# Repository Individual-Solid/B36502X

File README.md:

# BE6502X-SBC

## Overview
The BE6502X-SBC is an extensible single board computer, based on the "Hello World"
video tutorial by Ben Eater, and the "Potporri" computer design by Garth Wilson.

The computer features a W65c02 8-bit microprocessor running at 1Mhz, 32kb static 
RAM, 32kb EEPROM, two 8-bit GPIO ports, an onboard power supervisor, and a 40-pin
expansion bus.

The computer is "software compatible" with the programs Ben Eater builds in his
Youtube series. 

### Major Differences from the Ben Eater 6502 reference schematic
- Pull-up resistors on all active-low input signals (/NMI, /BE, etc...)
- Proper debounced reset pushbutton and power-on-reset circuit.
- Barrel jack 5v power connector, power LED, reset LED, SYNC LED, and switch.
- All 16 GPIO and 4 Control signals from the VIA are exposed through two
  14-pin shrouded pin IDC headers, CA2 also has an onboard LED.
- LCD, push-buttons, and 8-bit LED output are moved to an expansion board.
- Selector for 65c22 VIAs IRQ pin connection to processor /IRQ or /NMI

### Major Differences from the Garth Wilson 6502 reference schematic
- Clock option chosen is the Can Oscillator. Reset circuit chosen is DS1813.
- Because of these choices, an 74HC00 can be used for address decoding instead 
  of the '132
- Permanently configured for the WDC65c02 processor, 28C256 EEPROM.

## IO Ports
There are two onboard 8-bit IO ports connected to a W65c22S. Each port has an additional
two control lines. Each port has a 14-pin IDC male socket with the following pinout.
|Func|Pin#|Pin#|Func|
|----|-|-|---|
|GND|1|2|5V|
|Px0|3|4|Px1|
|Px2|5|6|Px3|
|Px4|7|8|Px5|
|Px6|9|10|Px7|
|Cx1|11|12|Cx2|
|5V|13|14|GND|

CA2 has an onboard indicator LED, but the pin can easily be repurposed.

## Bus

The BE6502X family sports a 40-pin extension bus. This bus is hardware compatible 
with RC2014 backplanes, although pin assignment is different. There's an existing 
small ecosystem of boards using the "RC6502" bus layout, but I invented my own 
think that felt natural to me. The original RC2014 bus has a lot of Z80/8080 
exclusive signals.

|Pin|BE6502X|RC6502|RC2014|Notes (primarily differences from RC6502)|
|-----|-------|------|------|-----|
| 1|A15|A15|A15||
| 2|A14|A14|A14||
| 3|A13|A13|A13||
| 4|A12|A12|A12||
| 5|A11|A11|A11||
| 6|A10|A10|A10||
| 7|A9|A9|A9||
| 8|A8|A8|A8||
| 9|A7|A7|A7||
|10|A6|A6|A6||
|11|A5|A5|A5||
|12|A4|A4|A4||
|13|A3|A3|A3||
|14|A2|A2|A2||
|15|A1|A1|A1||
|16|A0|A0|A0||
|17|GND|GND|GND||
|18|VCC|VCC|VCC||
|19|/MLB|PHI2O|/M1|See CLK for why it's not PHI2O. 6502 has no /M1. This could be SYNC, but /MLB is more interesting for DMA|
|20|/RESET|/RESET|/RESET||
|21|CLK|PHI0I|CLK|Using PHI1 in and PHI2 out is not supported for the new W65c22 chips used in the Eater kit. Just using PHI2 as CLK opens up an additional signal.|
|22|/IRQ|/IRQ|/INT||
|23|/BE|PHI1I (but really,EX0)|/MREQ|Dedicated /BE line for DMA|
|24|RWB|RWB|/WR||
|25|RDY|RDY|/RD||
|26|EX0|SYNC|/IOREQ|SYNC on the bus isn't particularly useful, compared to having an easy EX pin which you can easily connect to /IOEN|
|27|D0|D0|D0||
|28|D1|D1|D1||
|29|D2|D2|D2||
|30|D3|D3|D3||
|31|D4|D4|D4||
|32|D5|D5|D5||
|33|D6|D6|D6||
|34|D7|D7|D7||
|35|SDA|Tx|Tx|Putting the UART lines on the bus isn't particularly useful. I'm not aware of any meaningful uses where another module wanted the primary UART.|
|36|SCL|Rx|Rx|So instead, these are dedicated for I2C devices. There's no I2C master on the SBC, but there's also not a UART.|
|37|/NMI|/NMI|U1||
|38|EX1|EX1|U2||
|39|EX2|EX2|U3||
|40|GND|EX3|U4|Another GND line never hurt anyone.|

Next to the bus on the mainboard (Garth-1 based) are jumpers for the following signals, allowing
easy assignment to an EX line on the Bus, or for direct jumping to another board.

|Pin|Signal|
|-|-|
|1|SYNC|
|2|/VP|
|3|/RAMSEL|
|4|/IOSEL|

## Expansion Cards

Expansion cards connect to the BE6502X bus, with the exception of the Eater Experiment
card, which connects directly to the IO Ports! These are all the hopes and dreams and 
not yet designed.

### Dual IO and UART
2nd 65c22 VIA, 65c51 UART

### Arduino Mega Bus Monitor
Connect an Arduino Mega 2560 to monitor the bus and provide a low speed clock. Can
also use the Mega as a RAM Programmer/"bootloader".

### Ben Eater Experiment Card
Uses the IO Port A&B 14-pin connectors, adds a 2x20 LCD display and five push
buttons. A jumper is provided for 4-bit or 8-bit mode on the LCD, and the
push buttons are wire-OR'd together to CA1 for optional interrupt control.
Both the screen contrast and backlight are adjustable by onboard potentiometers.

## References
- RC6502 Bus design notes (and related subjects). https://github.com/tebl/RC6502-Apple-1-Replica/blob/master/Bus.md
- Ben Eater "Hello World" series home with schematic and videos. https://eater.net/6502
- Garth Wilson's 6502 Primer, including "Potporri" schematic, and countless other useful references. https://wilsonminesco.com/6502primer/potpourri.html#BAS_CPU
- Stephen Cousin's "Small Computer Central" with design notes on RC2014 backplanes, and a good source of the SC141 modular backplane and the SC142 Power Supply Module. https://smallcomputercentral.wordpress.com/kits/

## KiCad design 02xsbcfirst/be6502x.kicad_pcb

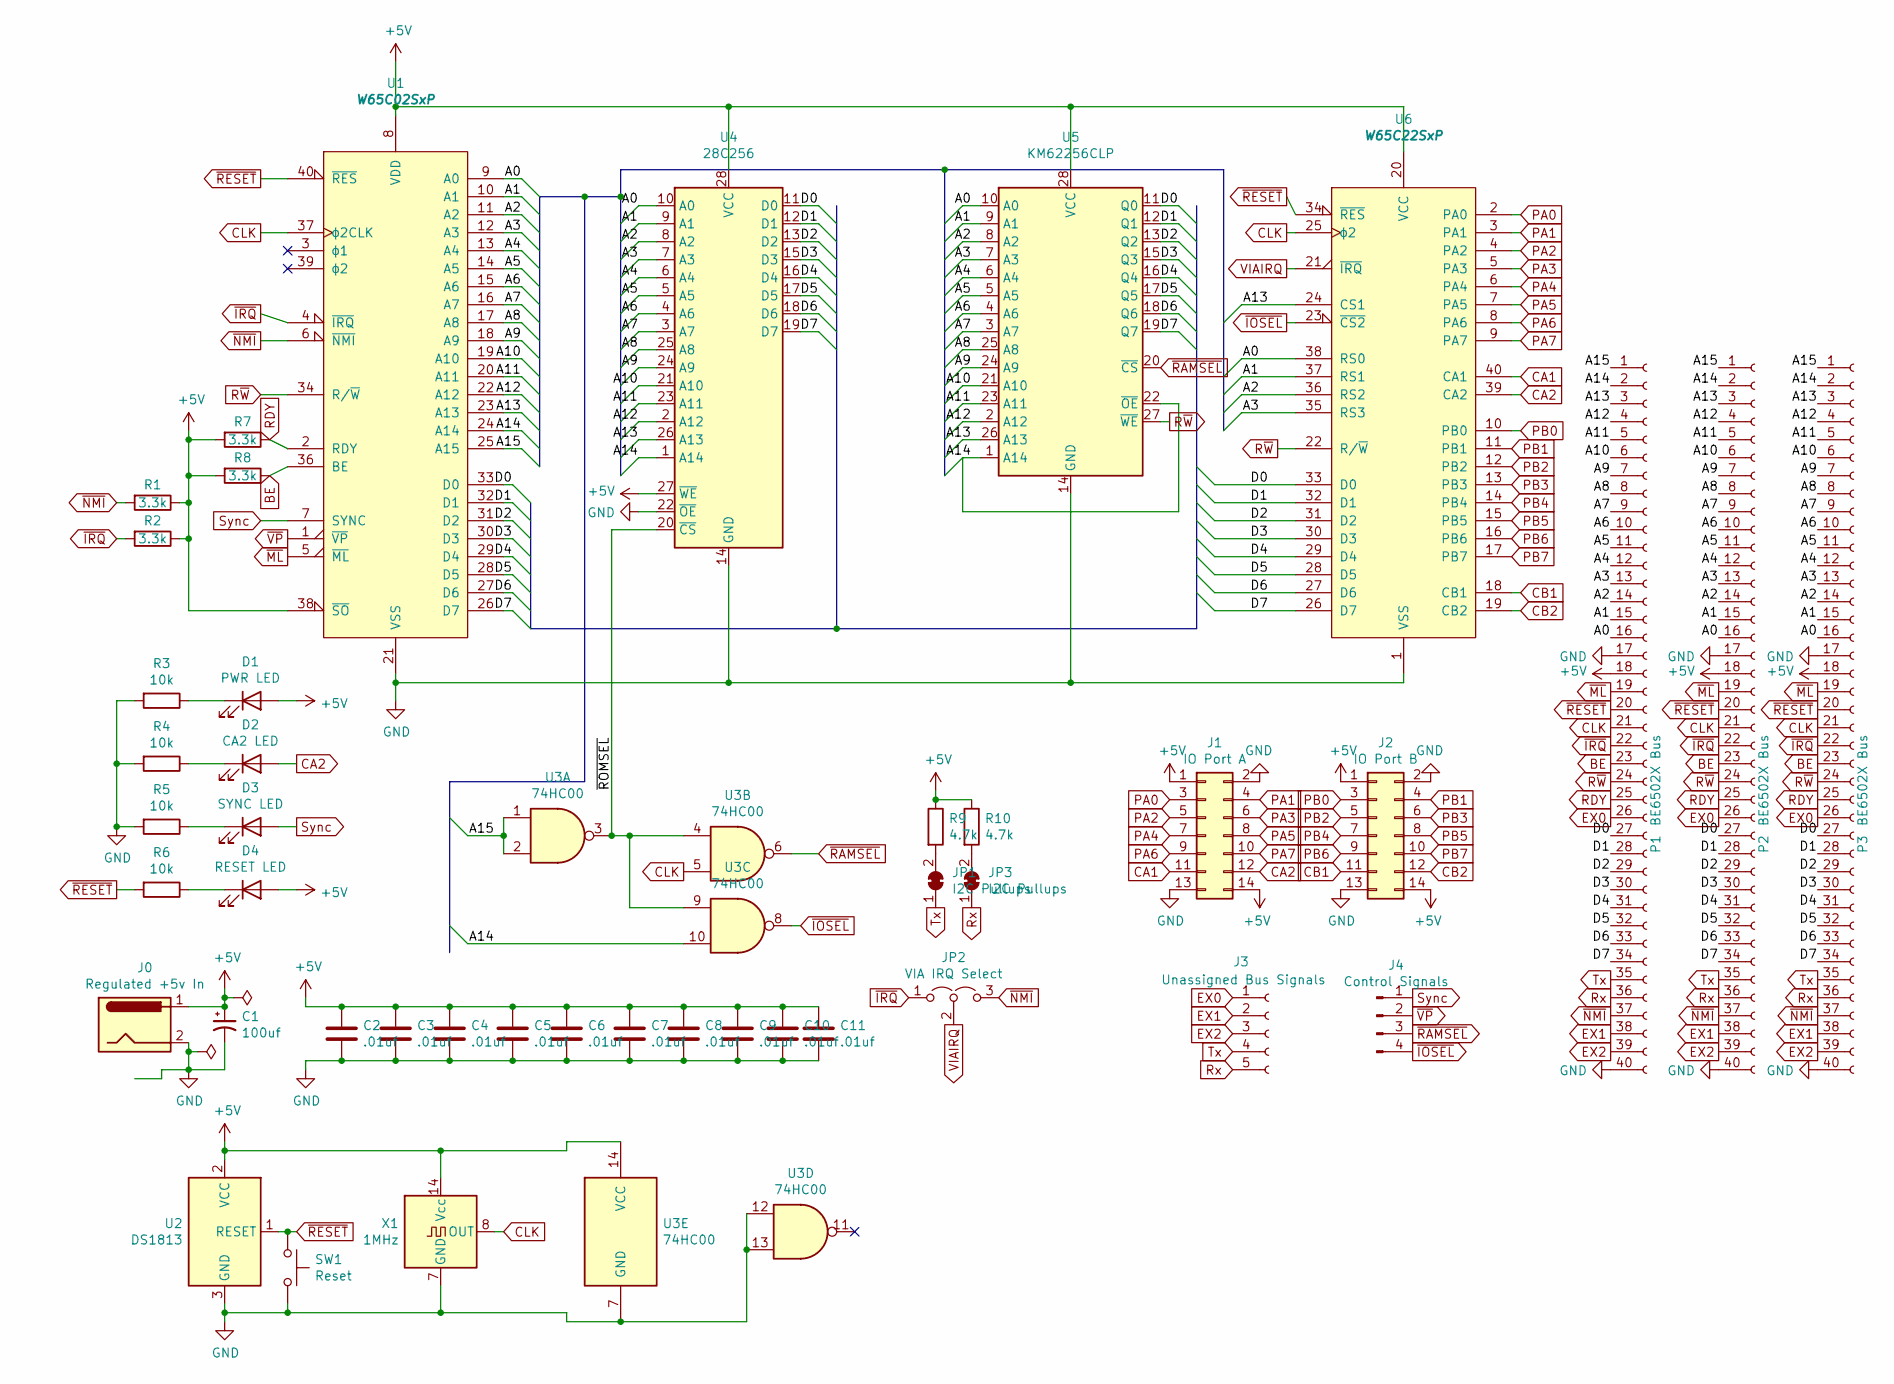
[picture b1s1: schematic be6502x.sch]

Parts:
C1: 100uf; CP_Radial_D4.0mm_P2.00mm
C2, C3, C4, C5, C6, C7, C8, C9, C10, C11: .01uf; C_Disc_D3.0mm_W2.0mm_P2.50mm
D1: PWR LED; LED_D4.0mm
D2: CA2 LED; LED_D4.0mm
D3: SYNC LED; LED_D4.0mm
D4: RESET LED; LED_D4.0mm
J0: Regulated +5v In; BarrelJack_Horizontal
J1: IO Port A; IDC-Header_2x07_P2.54mm_Vertical
J2: IO Port B; IDC-Header_2x07_P2.54mm_Vertical
J3: Unassigned Bus Signals; PinSocket_1x05_P2.54mm_Vertical
J4: Control Signals; PinHeader_1x04_P2.54mm_Vertical
JP1, JP3: I2C Pullups; SolderJumper-2_P1.3mm_Bridged_Pad1.0x1.5mm
JP2: VIA IRQ Select; PinHeader_1x03_P2.54mm_Vertical
P1, P2, P3: BE6502X Bus; PinSocket_1x40_P2.54mm_Vertical
R1, R2, R7, R8: 3.3k; R_Axial_DIN0207_L6.3mm_D2.5mm_P7.62mm_Horizontal
R3, R4, R5, R6: 10k; R_Axial_DIN0207_L6.3mm_D2.5mm_P7.62mm_Horizontal
R9, R10: 4.7k; R_Axial_DIN0207_L6.3mm_D2.5mm_P7.62mm_Horizontal
SW1: Reset; SW_PUSH_6mm
U1: W65C02SxP; DIP-40_W15.24mm_Socket
U2: DS1813; TO-92
U3: 74HC00; DIP-14_W7.62mm_Socket
U4: 28C256; DIP_Socket-28_W11.9_W12.7_W15.24_W17.78_W18.5_3M_228-1277-0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
U5: KM62256CLP; DIP-28_W15.24mm_Socket
U6: W65C22SxP; DIP-40_W15.24mm_Socket
X1: 1MHz; Oscillator_DIP-14

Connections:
+5V: C1.1, C2.1, C3.1, C4.1, C5.1, C6.1, C7.1, C8.1, C9.1, C10.1, C11.1, D1.2 (A), D4.2 (A), J0.1, J1.1, J1.14, J2.1, J2.14, P1.18, P2.18, P3.18, R1.1, R2.1, R7.2, R8.2, R9.1, R10.1, U1.8 (VDD), U1.38 (~SO), U2.2 (VCC), U3.14 (VCC), U4.27 (~WE), U4.28 (VCC), U5.28 (VCC), U6.20 (VCC), X1.14 (Vcc)
/A0: P1.16, P2.16, P3.16, U1.9 (A0), U4.10 (A0), U5.10 (A0), U6.38 (RS0)
/A1: P1.15, P2.15, P3.15, U1.10 (A1), U4.9 (A1), U5.9 (A1), U6.37 (RS1)
/A2: P1.14, P2.14, P3.14, U1.11 (A2), U4.8 (A2), U5.8 (A2), U6.36 (RS2)
/A3: P1.13, P2.13, P3.13, U1.12 (A3), U4.7 (A3), U5.7 (A3), U6.35 (RS3)
/A4: P1.12, P2.12, P3.12, U1.13 (A4), U4.6 (A4), U5.6 (A4)
/A5: P1.11, P2.11, P3.11, U1.14 (A5), U4.5 (A5), U5.5 (A5)
/A6: P1.10, P2.10, P3.10, U1.15 (A6), U4.4 (A6), U5.4 (A6)
/A7: P1.9, P2.9, P3.9, U1.16 (A7), U4.3 (A7), U5.3 (A7)
/A8: P1.8, P2.8, P3.8, U1.17 (A8), U4.25 (A8), U5.25 (A8)
/A9: P1.7, P2.7, P3.7, U1.18 (A9), U4.24 (A9), U5.24 (A9)
/A10: P1.6, P2.6, P3.6, U1.19 (A10), U4.21 (A10), U5.21 (A10)
/A11: P1.5, P2.5, P3.5, U1.20 (A11), U4.23 (A11), U5.23 (A11)
/A12: P1.4, P2.4, P3.4, U1.22 (A12), U4.2 (A12), U5.2 (A12)
/A13: P1.3, P2.3, P3.3, U1.23 (A13), U4.26 (A13), U5.26 (A13), U6.24 (CS1)
/A14: P1.2, P2.2, P3.2, U1.24 (A14), U3.10, U4.1 (A14), U5.1 (A14), U5.22 (~OE)
/A15: P1.1, P2.1, P3.1, U1.25 (A15), U3.1, U3.2
/D0: P1.27, P2.27, P3.27, U1.33 (D0), U4.11 (D0), U5.11 (Q0), U6.33 (D0)
/D1: P1.28, P2.28, P3.28, U1.32 (D1), U4.12 (D1), U5.12 (Q1), U6.32 (D1)
/D2: P1.29, P2.29, P3.29, U1.31 (D2), U4.13 (D2), U5.13 (Q2), U6.31 (D2)
/D3: P1.30, P2.30, P3.30, U1.30 (D3), U4.15 (D3), U5.15 (Q3), U6.30 (D3)
/D4: P1.31, P2.31, P3.31, U1.29 (D4), U4.16 (D4), U5.16 (Q4), U6.29 (D4)
/D5: P1.32, P2.32, P3.32, U1.28 (D5), U4.17 (D5), U5.17 (Q5), U6.28 (D5)
/D6: P1.33, P2.33, P3.33, U1.27 (D6), U4.18 (D6), U5.18 (Q6), U6.27 (D6)
/D7: P1.34, P2.34, P3.34, U1.26 (D7), U4.19 (D7), U5.19 (Q7), U6.26 (D7)
/~ROMSEL~: U3.3, U3.4, U3.9, U4.20 (~CS)
BE: P1.23, P2.23, P3.23, R8.1, U1.36 (BE)
CA1: J1.11, U6.40 (CA1)
CA2: D2.2 (A), J1.12, U6.39 (CA2)
CB1: J2.11, U6.18 (CB1)
CB2: J2.12, U6.19 (CB2)
CLK: P1.21, P2.21, P3.21, U1.37 (ϕ2CLK), U3.5, U6.25 (ϕ2), X1.8 (OUT)
EX0: J3.1, P1.26, P2.26, P3.26
EX1: J3.2, P1.38, P2.38, P3.38
EX2: J3.3, P1.39, P2.39, P3.39
GND: C1.2, C2.2, C3.2, C4.2, C5.2, C6.2, C7.2, C8.2, C9.2, C10.2, C11.2, J0.2, J1.2, J1.13, J2.2, J2.13, P1.17, P1.40, P2.17, P2.40, P3.17, P3.40, R3.2, R4.2, R5.2, SW1.2, U1.21 (VSS), U2.3 (GND), U3.7 (GND), U3.12, U3.13, U4.14 (GND), U4.22 (~OE), U5.14 (GND), U6.1 (VSS), X1.7 (GND)
unnamed: D1.1 (K), R3.1
unnamed: D2.1 (K), R4.1
unnamed: D3.1 (K), R5.1
unnamed: D4.1 (K), R6.1
unnamed: JP1.2 (B), R9.2
unnamed: JP3.2 (B), R10.2
PA0: J1.3, U6.2 (PA0)
PA1: J1.4, U6.3 (PA1)
PA2: J1.5, U6.4 (PA2)
PA3: J1.6, U6.5 (PA3)
PA4: J1.7, U6.6 (PA4)
PA5: J1.8, U6.7 (PA5)
PA6: J1.9, U6.8 (PA6)
PA7: J1.10, U6.9 (PA7)
PB0: J2.3, U6.10 (PB0)
PB1: J2.4, U6.11 (PB1)
PB2: J2.5, U6.12 (PB2)
PB3: J2.6, U6.13 (PB3)
PB4: J2.7, U6.14 (PB4)
PB5: J2.8, U6.15 (PB5)
PB6: J2.9, U6.16 (PB6)
PB7: J2.10, U6.17 (PB7)
RDY: P1.25, P2.25, P3.25, R7.1, U1.2 (RDY)
Rx: J3.5, JP3.1 (A), P1.36, P2.36, P3.36
R~W~: P1.24, P2.24, P3.24, U1.34 (R/~W), U5.27 (~WE), U6.22 (R/~W)
Sync: D3.2 (A), J4.1, U1.7 (SYNC)
Tx: J3.4, JP1.1 (A), P1.35, P2.35, P3.35
VIAIRQ: JP2.2 (C), U6.21 (~IRQ)
~IOSEL~: J4.4, U3.8, U6.23 (~CS2)
~IRQ~: JP2.1 (A), P1.22, P2.22, P3.22, R2.2, U1.4 (~IRQ)
~ML~: P1.19, P2.19, P3.19, U1.5 (~ML)
~NMI~: JP2.3 (B), P1.37, P2.37, P3.37, R1.2, U1.6 (~NMI)
~RAMSEL~: J4.3, U3.6, U5.20 (~CS)
~RESET~: P1.20, P2.20, P3.20, R6.2, SW1.1, U1.40 (~RES), U2.1 (RESET), U6.34 (~RES)
~VP~: J4.2, U1.1 (~VP)

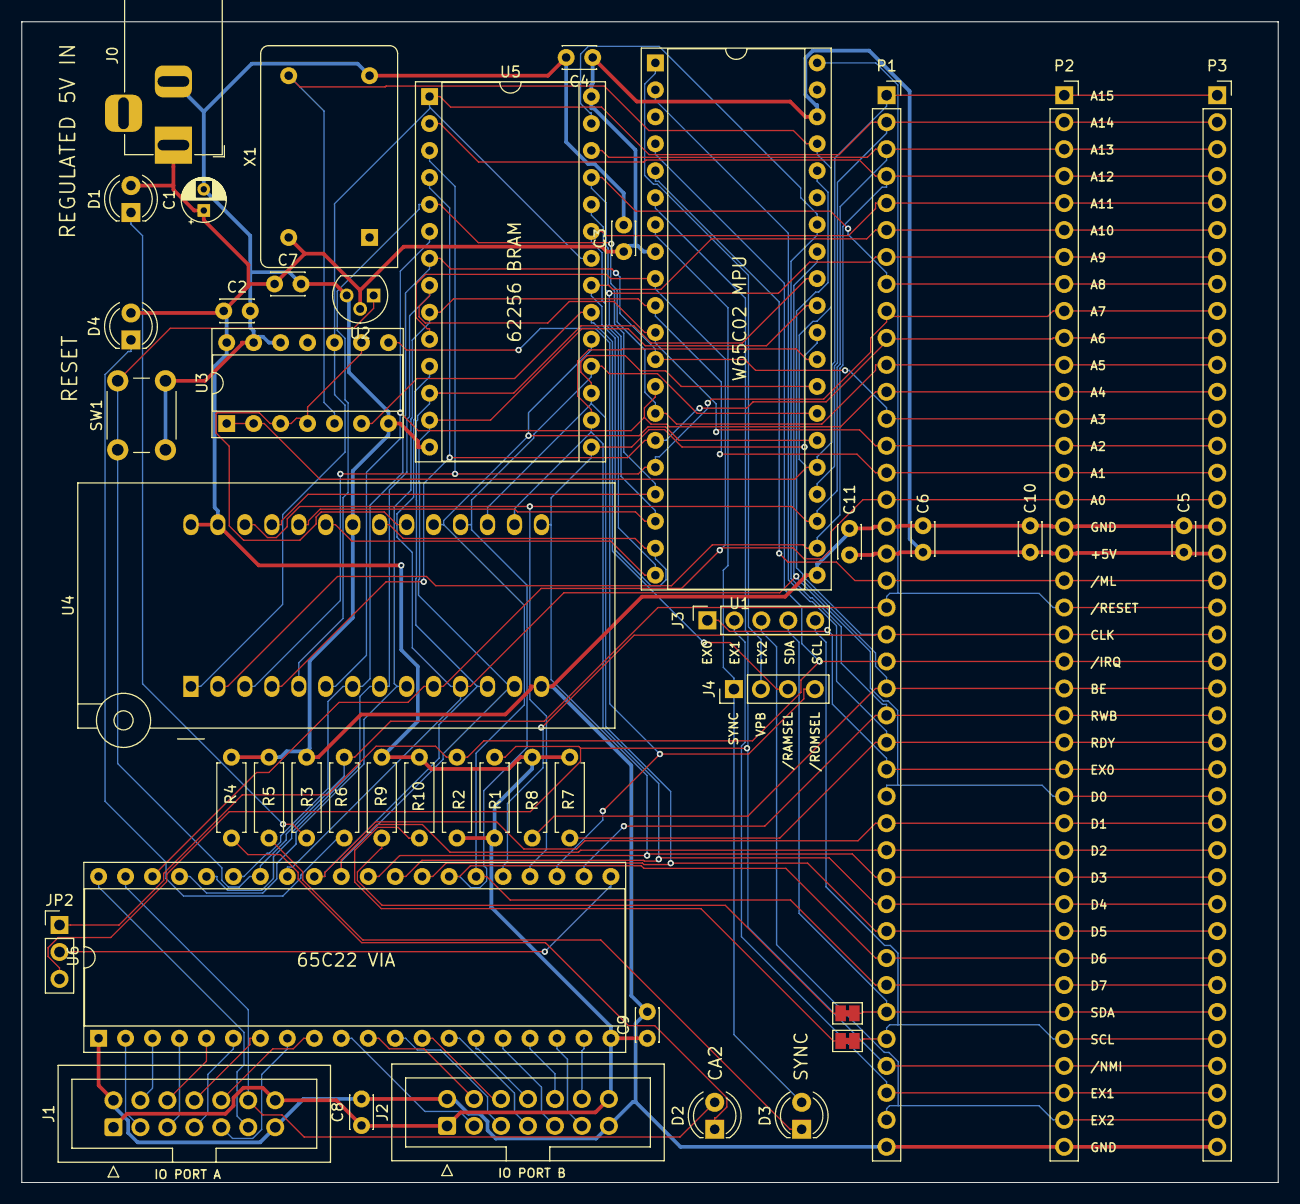
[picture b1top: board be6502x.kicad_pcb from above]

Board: 2 copper layers, 118.4 x 109.3 mm, 44 parts (0 on the bottom side), 71 nets.

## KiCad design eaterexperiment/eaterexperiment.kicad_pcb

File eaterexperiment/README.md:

# Eater Experiment Board

The Eater Experiment Board connects to the two IO Ports on the BE6502x SBC, and
breaks out LEDS, buttons, and a header for a 2x20 character LCD. This board lets
you run all the 6522 example code on Ben Eater's 6502 project website, AND has
extra LEDs and buttons connected for additional experimenting.

This is a very simple board, with only one "configuration" option. There's a 
jumper to select whether the LCD should be in normal 8-bit mode, or have all
of its IO on Port B, using 4-bit mode. 

UGH EVERYTHING HERE ON SUX.Plug in both IDC cables, select your mode,
attach the LCD, and you're ready to go.

Both IO Ports have indicator LEDs on all 8 bidirectional data lines as well as
both control lines. That's a total of 20 blinkenable-lites! The ten signals 
that compose port A also have input pushbuttons (tied high, push closes it to
ground). This makes this a great board for prototyping input devices or doing
the same experiments as in Ben's youtube videos.

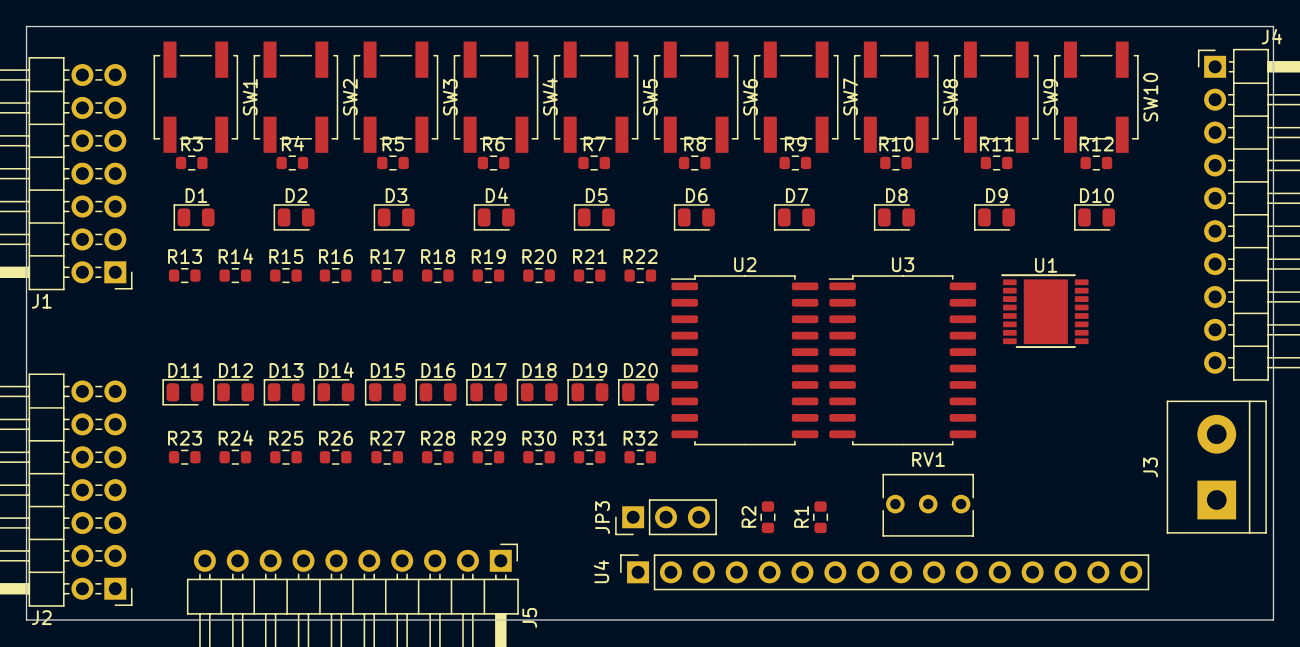
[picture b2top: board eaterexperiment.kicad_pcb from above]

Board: 2 copper layers, 96.3 x 45.8 mm, 73 parts (0 on the bottom side), 66 nets, no tracks yet.

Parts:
D1, D2, D3, D4, D5, D6, D7, D8, D9, D10, D11, D12, D13, D14, D15, D16, D17, D18, D19, D20: LED; LED_0805_2012Metric
J1: IO Port A; PinHeader_2x07_P2.54mm_Horizontal
J2: IO Port B; PinHeader_2x07_P2.54mm_Horizontal
J3: 5v Out; TerminalBlock_bornier-2_P5.08mm
J4: Port A; PinHeader_1x10_P2.54mm_Horizontal
J5: Port B; PinHeader_1x10_P2.54mm_Horizontal
JP3: Mode Sel; PinHeader_1x03_P2.54mm_Vertical
R1, R2, R3, R4, R5, R6, R7, R8, R9, R10, R11, R12, R13, R14, R15, R16, R17, R18, R19, R20, R21, R22, R23, R24, R25, R26, R27, R28, R29, R30, R31, R32: 4.7k; R_0603_1608Metric
RV1: R_POT_TRIM; Potentiometer_Bourns_3266Y_Vertical
SW1, SW2, SW3, SW4, SW5, SW6, SW7, SW8, SW9, SW10: Push; SW_Push_1P1T_NO_CK_KSC6xxJ
U1: 74HC157; HTSSOP-16-1EP_4.4x5mm_P0.65mm_EP3.4x5mm
U2, U3: 74HC245; SOIC-20W_7.5x12.8mm_P1.27mm
U4: HD44780; PinSocket_1x16_P2.54mm_Vertical

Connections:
CA1: J1.11, J4.9, R21.1, U1.3
CA2: J1.12, J4.10, R22.1
CB1: J2.11, J5.2, R31.1, U1.2
CB2: J2.12, J5.1, R32.1
GND: D1.1, D2.1, D3.1, D4.1, D5.1, D6.1, D7.1, D8.1, D9.1, D10.1, D11.1, D12.1, D13.1, D14.1, D15.1, D16.1, D17.1, D18.1, D19.1, D20.1, J1.2, J1.13, J2.2, J2.13, J3.1, JP3.2, RV1.1, SW1.1, SW2.1, SW3.1, SW4.1, SW5.1, SW6.1, SW7.1, SW8.1, SW9.1, SW10.1, U1.8, U1.15, U2.10, U3.10, U4.1, U4.16
unnamed: D1.2, R13.2
unnamed: D2.2, R14.2
unnamed: D3.2, R15.2
unnamed: D4.2, R16.2
unnamed: D5.2, R17.2
unnamed: D6.2, R18.2
unnamed: D7.2, R19.2
unnamed: D8.2, R20.2
unnamed: D9.2, R21.2
unnamed: D10.2, R22.2
unnamed: D11.2, R23.2
unnamed: D12.2, R24.2
unnamed: D13.2, R25.2
unnamed: D14.2, R26.2
unnamed: D15.2, R27.2
unnamed: D16.2, R28.2
unnamed: D17.2, R29.2
unnamed: D18.2, R30.2
unnamed: D19.2, R31.2
unnamed: D20.2, R32.2
unnamed: R3.1, SW1.2
unnamed: R4.1, SW2.2
unnamed: R5.1, SW3.2
unnamed: R6.1, SW4.2
unnamed: R7.1, SW5.2
unnamed: R8.1, SW6.2
unnamed: R9.1, SW7.2
unnamed: R10.1, SW8.2
unnamed: R11.1, SW9.2
unnamed: R12.1, SW10.2
unnamed: RV1.2, U4.3
unnamed: U1.7, U4.6
unnamed: U1.9, U4.5
unnamed: U1.12, U4.4
unnamed: U2.2, U4.7
unnamed: U2.3, U4.8
unnamed: U2.4, U4.9
unnamed: U2.5, U4.10
unnamed: U2.6, U3.2, U4.11
unnamed: U2.7, U3.3, U4.12
unnamed: U2.8, U3.4, U4.13
unnamed: U2.9, U3.5, U4.14
PA0: J1.3, J4.1, R13.1
PA1: J1.4, J4.2, R14.1
PA2: J1.5, J4.3, R15.1
PA3: J1.6, J4.4, R16.1
PA4: J1.7, J4.5, R17.1
PA5: J1.8, J4.6, R18.1, U1.13
PA6: J1.9, J4.7, R19.1, U1.10, U2.1
PA7: J1.10, J4.8, R20.1, U1.6
PB0: J2.3, J5.10, R23.1, U2.18, U3.18
PB1: J2.4, J5.9, R24.1, U2.17, U3.17
PB2: J2.5, J5.8, R25.1, U2.16, U3.16
PB3: J2.6, J5.7, R26.1, U2.15, U3.15
PB4: J2.7, J5.6, R27.1, U1.14, U2.14, U3.14
PB5: J2.8, J5.5, R28.1, U1.11, U2.13, U3.1, U3.13
PB6: J2.9, J5.4, R29.1, U1.5, U2.12, U3.12
PB7: J2.10, J5.3, R30.1, U2.11, U3.11
VCC: J1.1, J1.14, J2.1, J2.14, J3.2, R1.2, R2.2, R3.2, R4.2, R5.2, R6.2, R7.2, R8.2, R9.2, R10.2, R11.2, R12.2, U1.16, U2.20, U3.20, U4.2, U4.15
~EN4~: JP3.3, R1.1, U1.1, U3.19
~EN8~: JP3.1, R2.1, U2.19

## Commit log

2021-09-04 trying to get actions working
2021-09-04 being specific
2021-09-04 try a different kibot conf
